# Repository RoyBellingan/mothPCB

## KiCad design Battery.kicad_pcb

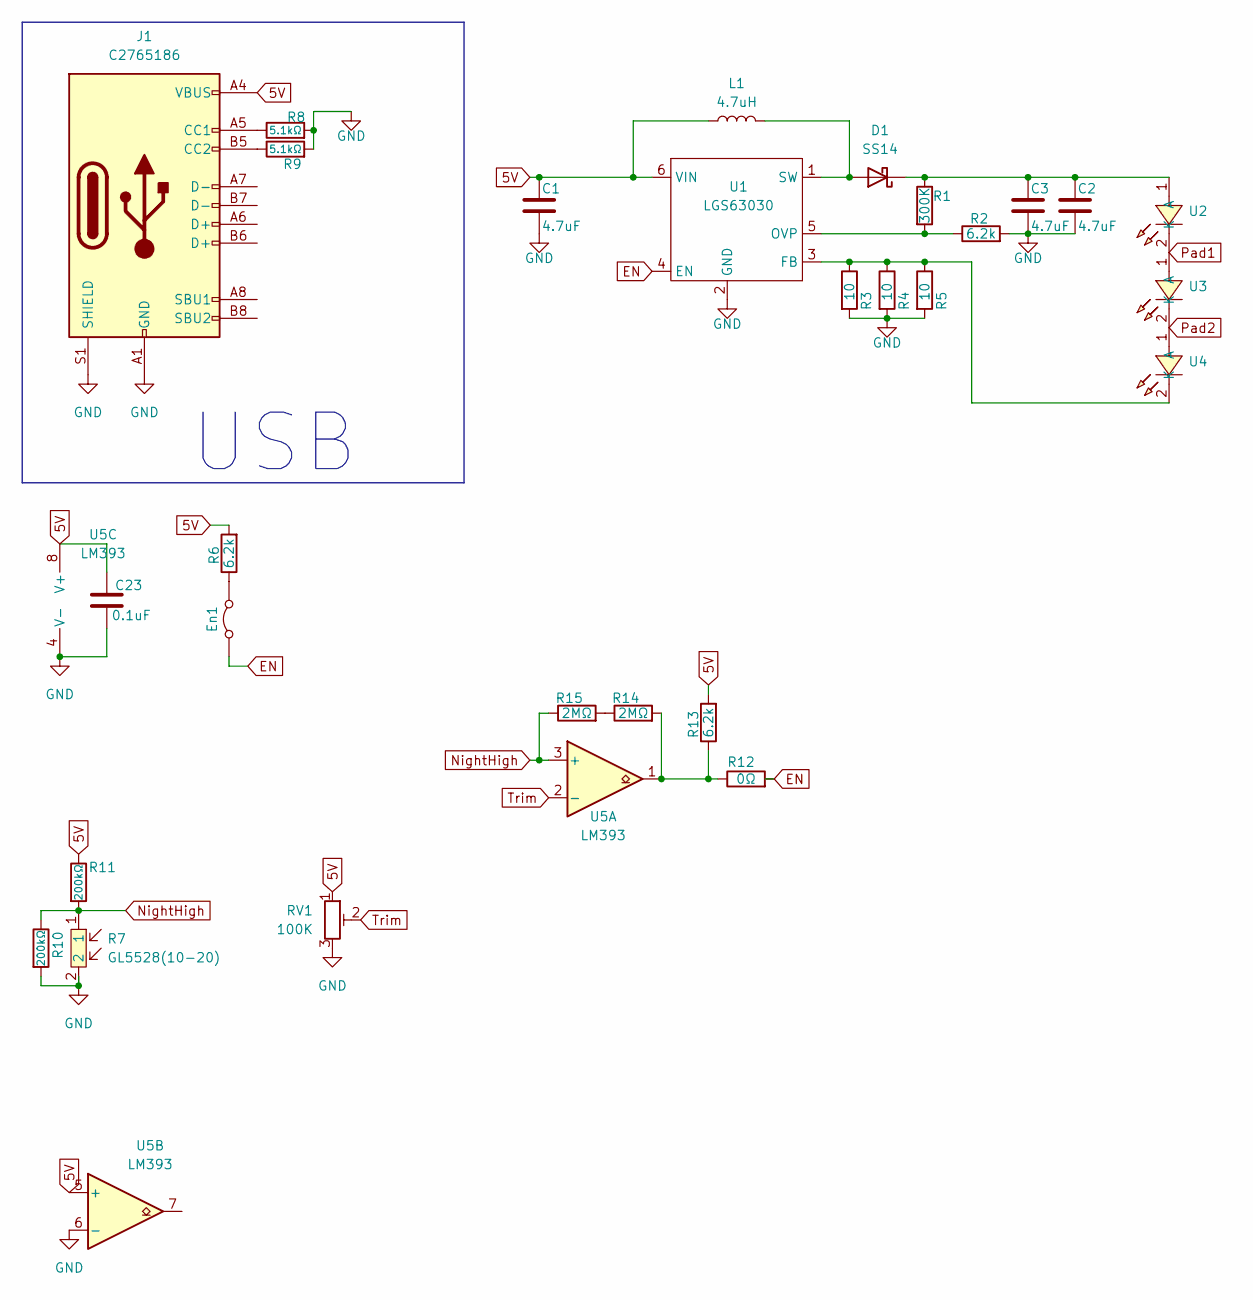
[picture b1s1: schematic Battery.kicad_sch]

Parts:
C1, C2, C3: 4.7uF; C_0805_2012Metric; LCSC C1779
C23: C1525; C_0402_1005Metric
D1: SS14; D_SMA
En1: Jumper_2_Bridged; TestPoint_2Pads_Pitch2.54mm_Drill0.8mm
J1: C2765186; USB_C_Receptacle_G-Switch_GT-USB-7010ASV
L1: 4.7uH; L_0805_2012Metric; LCSC C87543
R1: 300K; R_0603_1608Metric; LCSC C23024
R2, R6, R13: 6.2k; R_0603_1608Metric; LCSC C4260
R3, R4, R5: 10; R_0603_1608Metric; LCSC C22859
R7: GL5528(10-20); RES-TH_L5.1-W4.3-P3.40-D0.5; LCSC Part C10081
R8, R9: C25905; R_0402_1005Metric
R10, R11: C25764; R_0402_1005Metric
R12: C17888; R_1206_3216Metric_Pad1.30x1.75mm_HandSolder
R14, R15: 2MΩ; R_0603_1608Metric; LCSC C22976
RV1: 100K; Potentiometer_Bourns_3339S_Horizontal; LCSC C118966
U1: LGS63030; SOT-23-6_L2.9-W1.6-P0.95-LS2.8-BR; LCSC Part C5123976
U2, U3, U4: JNJ-LTAU0106W90/Q15MIL/365-370NM; LED-SMD_L3.5-W2.8-FD_GREEN-1; LCSC Part C7500133
U5: LM393; SOIC-8_3.9x4.9mm_P1.27mm

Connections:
5V: C1.1, C23.1, J1.A4 (VBUS), J1.A9 (VBUS), J1.B4 (VBUS), J1.B9 (VBUS), L1.1, R6.2, R11.1, R13.2, RV1.1, U1.6 (VIN), U5.5 (+), U5.8 (V+)
EN: En1.1 (A), R12.2, U1.4 (EN)
GND: C1.2, C2.2, C3.2, C23.2, J1.A1 (GND), J1.A12 (GND), J1.B1 (GND), J1.B12 (GND), J1.S1 (SHIELD), R2.2, R3.2, R4.2, R5.2, R7.2, R8.2, R9.2, R10.2, RV1.3, U1.2 (GND), U5.4 (V-), U5.6 (-)
unnamed: D1.2 (A), L1.2, U1.1 (SW)
unnamed: C2.1, C3.1, D1.1 (K), R1.1, U2.1 (A)
unnamed: En1.2 (B), R6.1
unnamed: J1.A5 (CC1), R8.1
unnamed: J1.B5 (CC2), R9.1
unnamed: R12.1, R13.1, R14.2, U5.1
unnamed: R14.1, R15.2
unnamed: R3.1, R4.1, R5.1, U1.3 (FB), U4.2 (K)
unnamed: R1.2, R2.1, U1.5 (OVP)
NightHigh: R7.1, R10.1, R11.2, R15.1, U5.3 (+)
Pad1: U2.2 (K), U3.1 (A)
Pad2: U3.2 (K), U4.1 (A)
Trim: RV1.2, U5.2 (-)

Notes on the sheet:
USB

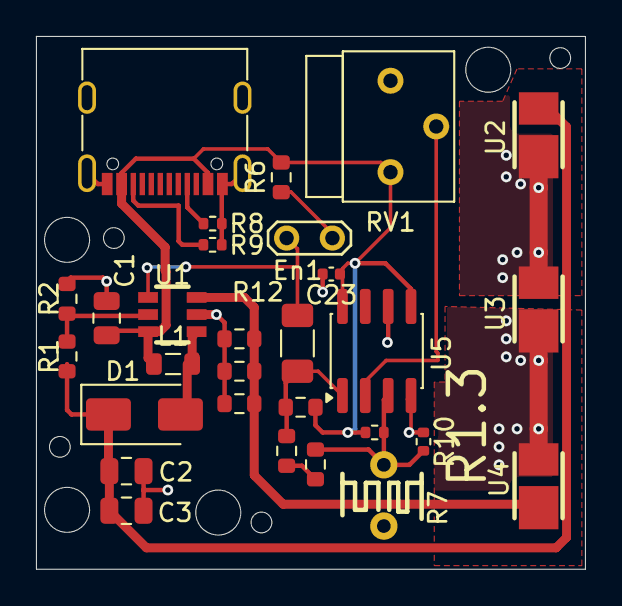
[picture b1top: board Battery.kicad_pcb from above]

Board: 2 copper layers, 30.5 x 29.6 mm, 29 parts (0 on the bottom side), 16 nets.

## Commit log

2026-02-10 R1.3
2026-02-10 rename
